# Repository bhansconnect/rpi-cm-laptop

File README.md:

<!--
SPDX-FileCopyrightText: 2021 The RPI CM Laptop Contributors

SPDX-License-Identifier: Apache-2.0
-->

# RPI CM Laptop

The goal of this project is to make a PCB that enables creation of a laptop that uses a Raspberry Pi Compute Module as the brains.
The laptop plans to use a mechanical keyboard and is meant to be a nice companion device for journaling and task management.

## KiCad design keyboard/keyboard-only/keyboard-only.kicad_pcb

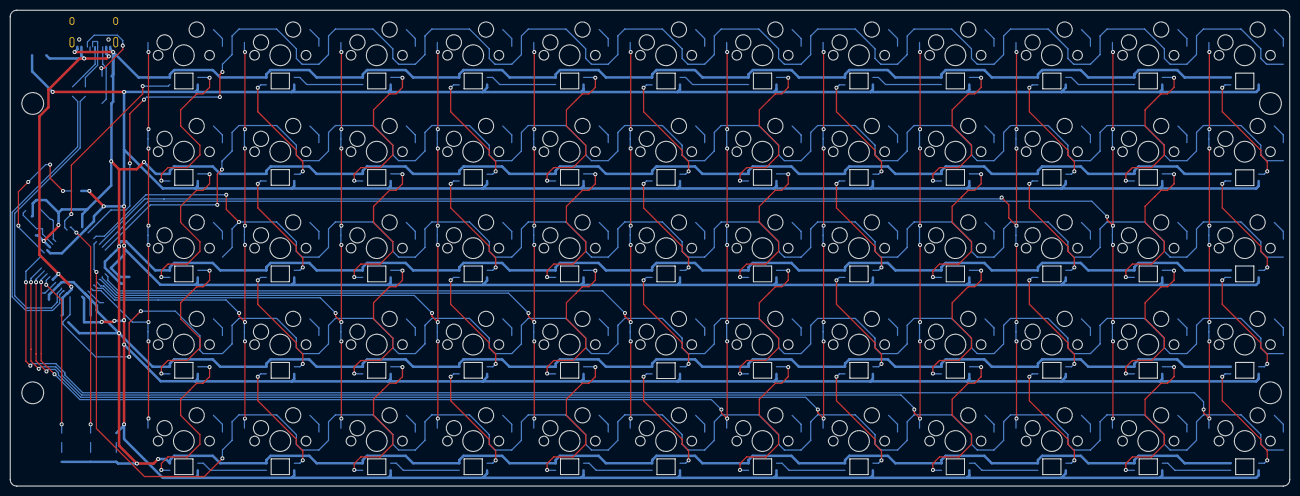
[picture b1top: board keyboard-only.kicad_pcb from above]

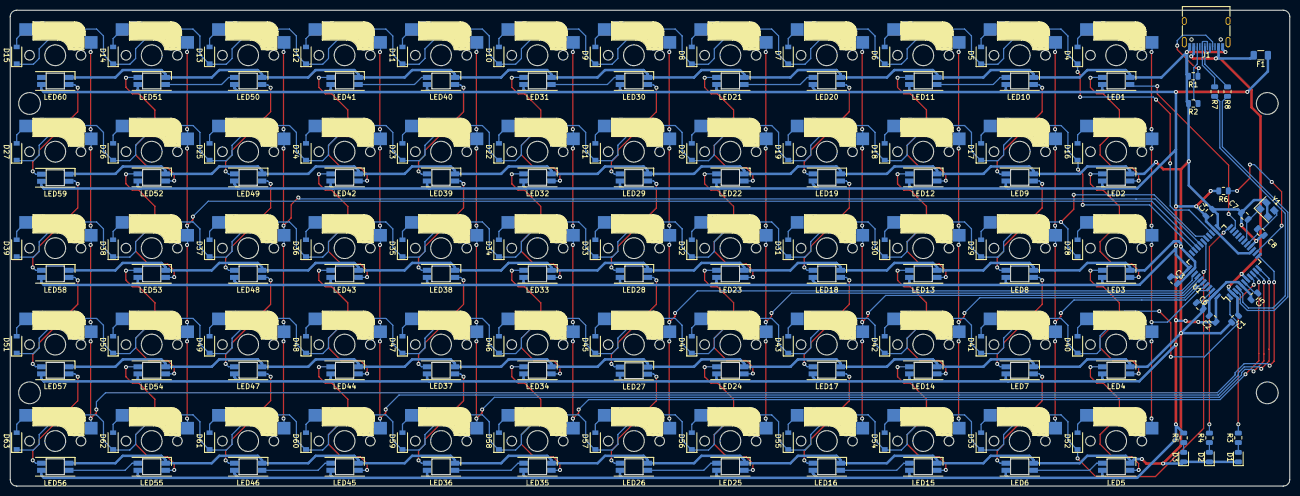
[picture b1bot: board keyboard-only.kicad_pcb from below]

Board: 2 copper layers, 252.7 x 94.0 mm, 207 parts (143 on the bottom side), 156 nets.

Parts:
C1, C3, C5: 1uF; C_0805_2012Metric
C2: 10uF; C_0805_2012Metric
C4, C6: 100nF; C_0805_2012Metric
C7, C8: 22pF; C_0805_2012Metric
D1: Yellow; LED_0805_2012Metric
D2: Green; LED_0805_2012Metric
D3: Red; LED_0805_2012Metric
D4, D5, D6, D7, D8, D9, D10, D11, D12, D13, D14, D15, D16, D17, D18, D19, D20, D21, D22, D23, D24, D25, D26, D27, D28, D29, D30, D31, D32, D33, D34, D35, D36, D37, D38, D39, D40, D41, D42, D43, D44, D45, D46, D47, D48, D49, D50, D51, D52, D53, D54, D55, D56, D57, D58, D59, D60, D61, D62, D63: D; D_SOD-123
F1: 500mA; Fuse_1206_3216Metric
J1: USB_C_Receptacle_USB2.0; USB_C_Receptacle_HRO_TYPE-C-31-M-12
LED1, LED2, LED3, LED4, LED5, LED6, LED7, LED8, LED9, LED10, LED11, LED12, LED13, LED14, LED15, LED16, LED17, LED18, LED19, LED20, LED21, LED22, LED23, LED24, LED25, LED26, LED27, LED28, LED29, LED30, LED31, LED32, LED33, LED34, LED35, LED36, LED37, LED38, LED39, LED40, LED41, LED42, LED43, LED44, LED45, LED46, LED47, LED48, LED49, LED50, LED51, LED52, LED53, LED54, LED55, LED56, LED57, LED58, LED59, LED60: YS-SK6812MINI-E
R1, R2: 5.1K; R_0805_2012Metric
R3, R4: 330; R_0805_2012Metric
R5: 1K; R_0805_2012Metric
R6: 10K; R_0805_2012Metric
R7, R8: 22; R_0805_2012Metric
Ref**: Val**; M2_HOLE_v2
Ref**#2, Ref**#3, Ref**#4: Val**; M2_HOLE_v2
SW1, SW2, SW3, SW4, SW5, SW6, SW7, SW8, SW9, SW10, SW11, SW12, SW13, SW14, SW15, SW16, SW17, SW18, SW19, SW20, SW21, SW22, SW23, SW24, SW25, SW26, SW27, SW28, SW29, SW30, SW31, SW32, SW33, SW34, SW35, SW36, SW37, SW38, SW39, SW40, SW41, SW42, SW43, SW44, SW45, SW46, SW47, SW48, SW49, SW50, SW51, SW52, SW53, SW54, SW55, SW56, SW57, SW58, SW59, SW60: SW_PUSH; CherryMX_Hotswap
U1: ATmega16U4-AU; TQFP-44_10x10mm_P0.8mm
Y1: 16MHz; Crystal_SMD_3225-4Pin_3.2x2.5mm

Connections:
COL0: SW1.1, SW13.1, SW25.1, SW37.1, SW49.1, U1.41
COL1: SW2.1, SW14.1, SW26.1, SW38.1, SW50.1, U1.40
COL2: SW3.1, SW15.1, SW27.1, SW39.1, SW51.1, U1.39
COL3: SW4.1, SW16.1, SW28.1, SW40.1, SW52.1, U1.38
COL4: SW5.1, SW17.1, SW29.1, SW41.1, SW53.1, U1.37
COL5: SW6.1, SW18.1, SW30.1, SW42.1, SW54.1, U1.36
COL6: SW7.1, SW19.1, SW31.1, SW43.1, SW55.1, U1.9
COL7: SW8.1, SW20.1, SW32.1, SW44.1, SW56.1, U1.10
COL8: SW9.1, SW21.1, SW33.1, SW45.1, SW57.1, U1.11
COL9: SW10.1, SW22.1, SW34.1, SW46.1, SW58.1, U1.29
COL10: SW11.1, SW23.1, SW35.1, SW47.1, SW59.1, U1.30
COL11: SW12.1, SW24.1, SW36.1, SW48.1, SW60.1, U1.12
D+: J1.A6, J1.B6, R7.2
D-: J1.A7, J1.B7, R8.2
GND: C1.2, C2.2, C3.2, C4.2, C5.2, C6.2, C7.2, C8.2, D1.1, D2.1, D3.1, J1.A1, J1.A12, J1.B1, J1.B12, LED1.3, LED2.3, LED3.3, LED4.3, LED5.3, LED6.3, LED7.3, LED8.3, LED9.3, LED10.3, LED11.3, LED12.3, LED13.3, LED14.3, LED15.3, LED16.3, LED17.3, LED18.3, LED19.3, LED20.3, LED21.3, LED22.3, LED23.3, LED24.3, LED25.3, LED26.3, LED27.3, LED28.3, LED29.3, LED30.3, LED31.3, LED32.3, LED33.3, LED34.3, LED35.3, LED36.3, LED37.3, LED38.3, LED39.3, LED40.3, LED41.3, LED42.3, LED43.3, LED44.3, LED45.3, LED46.3, LED47.3, LED48.3, LED49.3, LED50.3, LED51.3, LED52.3, LED53.3, LED54.3, LED55.3, LED56.3, LED57.3, LED58.3, LED59.3, LED60.3, R1.2, R2.2, U1.5, U1.15, U1.23, U1.33, U1.35, U1.43, Y1.2, Y1.4
unnamed: J1.A5, R1.1
unnamed: J1.B5, R2.1
unnamed: D3.2, R5.1
unnamed: D1.2, R3.1
unnamed: R3.2, U1.8
unnamed: D2.2, R4.1
unnamed: R4.2, U1.22
unnamed: R6.1, U1.13
unnamed: C5.1, U1.6
unnamed: C6.1, U1.42
unnamed: C7.1, U1.17, Y1.1
unnamed: C8.1, U1.16, Y1.3
unnamed: D4.2, SW1.2
unnamed: LED1.4, U1.21
unnamed: D5.2, SW2.2
unnamed: LED1.2, LED2.4
unnamed: D6.2, SW3.2
unnamed: LED2.2, LED3.4
unnamed: D7.2, SW4.2
unnamed: LED3.2, LED4.4
unnamed: D8.2, SW5.2
unnamed: LED4.2, LED5.4
unnamed: D9.2, SW6.2
unnamed: LED5.2, LED6.4
unnamed: D10.2, SW7.2
unnamed: LED6.2, LED7.4
unnamed: D11.2, SW8.2
unnamed: LED7.2, LED8.4
unnamed: D12.2, SW9.2
unnamed: LED8.2, LED9.4
unnamed: D13.2, SW10.2
unnamed: LED9.2, LED10.4
unnamed: D14.2, SW11.2
unnamed: LED10.2, LED11.4
unnamed: D15.2, SW12.2
unnamed: LED11.2, LED12.4
unnamed: D16.2, SW13.2
unnamed: LED12.2, LED13.4
unnamed: D17.2, SW14.2
unnamed: LED13.2, LED14.4
unnamed: D18.2, SW15.2
unnamed: LED14.2, LED15.4
unnamed: D19.2, SW16.2
unnamed: LED15.2, LED16.4
unnamed: D20.2, SW17.2
unnamed: LED16.2, LED17.4
unnamed: D21.2, SW18.2
unnamed: LED17.2, LED18.4
unnamed: D22.2, SW19.2
unnamed: LED18.2, LED19.4
unnamed: D23.2, SW20.2
unnamed: LED19.2, LED20.4
unnamed: D24.2, SW21.2
unnamed: LED20.2, LED21.4
unnamed: D25.2, SW22.2
unnamed: LED21.2, LED22.4
unnamed: D26.2, SW23.2
unnamed: LED22.2, LED23.4
unnamed: D27.2, SW24.2
unnamed: LED23.2, LED24.4
unnamed: D28.2, SW25.2
unnamed: LED24.2, LED25.4
unnamed: D29.2, SW26.2
unnamed: LED25.2, LED26.4
unnamed: D30.2, SW27.2
unnamed: LED26.2, LED27.4
unnamed: D31.2, SW28.2
unnamed: LED27.2, LED28.4
unnamed: D32.2, SW29.2
unnamed: LED28.2, LED29.4
unnamed: D33.2, SW30.2
unnamed: LED29.2, LED30.4
unnamed: D34.2, SW31.2
unnamed: LED30.2, LED31.4
unnamed: D35.2, SW32.2
unnamed: LED31.2, LED32.4
unnamed: D36.2, SW33.2
unnamed: LED32.2, LED33.4
unnamed: D37.2, SW34.2
unnamed: LED33.2, LED34.4
unnamed: D38.2, SW35.2
unnamed: LED34.2, LED35.4
unnamed: D39.2, SW36.2
unnamed: LED35.2, LED36.4
unnamed: D40.2, SW37.2
unnamed: LED36.2, LED37.4
unnamed: D41.2, SW38.2
unnamed: LED37.2, LED38.4
unnamed: D42.2, SW39.2
unnamed: LED38.2, LED39.4
unnamed: D43.2, SW40.2
unnamed: LED39.2, LED40.4
unnamed: D44.2, SW41.2
unnamed: LED40.2, LED41.4
unnamed: D45.2, SW42.2
unnamed: LED41.2, LED42.4
unnamed: D46.2, SW43.2
unnamed: LED42.2, LED43.4
unnamed: D47.2, SW44.2
unnamed: LED43.2, LED44.4
unnamed: D48.2, SW45.2
unnamed: LED44.2, LED45.4
unnamed: D49.2, SW46.2
unnamed: LED45.2, LED46.4
unnamed: D50.2, SW47.2
unnamed: LED46.2, LED47.4
unnamed: D51.2, SW48.2
unnamed: LED47.2, LED48.4
unnamed: D52.2, SW49.2
unnamed: LED48.2, LED49.4
unnamed: D53.2, SW50.2
unnamed: LED49.2, LED50.4
unnamed: D54.2, SW51.2
unnamed: LED50.2, LED51.4
unnamed: D55.2, SW52.2
unnamed: LED51.2, LED52.4
unnamed: D56.2, SW53.2
unnamed: LED52.2, LED53.4
unnamed: D57.2, SW54.2
unnamed: LED53.2, LED54.4
unnamed: D58.2, SW55.2
unnamed: LED54.2, LED55.4
unnamed: D59.2, SW56.2
unnamed: LED55.2, LED56.4
unnamed: D60.2, SW57.2
unnamed: LED56.2, LED57.4
unnamed: D61.2, SW58.2
unnamed: LED57.2, LED58.4
unnamed: D62.2, SW59.2
unnamed: LED58.2, LED59.4
unnamed: D63.2, SW60.2
unnamed: LED59.2, LED60.4
RD+: R7.1, U1.4
RD-: R8.1, U1.3
ROW0: D4.1, D5.1, D6.1, D7.1, D8.1, D9.1, D10.1, D11.1, D12.1, D13.1, D14.1, D15.1, U1.25
ROW1: D16.1, D17.1, D18.1, D19.1, D20.1, D21.1, D22.1, D23.1, D24.1, D25.1, D26.1, D27.1, U1.31
ROW2: D28.1, D29.1, D30.1, D31.1, D32.1, D33.1, D34.1, D35.1, D36.1, D37.1, D38.1, D39.1, U1.27
ROW3: D40.1, D41.1, D42.1, D43.1, D44.1, D45.1, D46.1, D47.1, D48.1, D49.1, D50.1, D51.1, U1.1
ROW4: D52.1, D53.1, D54.1, D55.1, D56.1, D57.1, D58.1, D59.1, D60.1, D61.1, D62.1, D63.1, U1.28
VBUS: C1.1, F1.1, J1.A4, J1.A9, J1.B4, J1.B9, U1.2, U1.7
VCC: C2.1, C3.1, C4.1, F1.2, LED1.1, LED2.1, LED3.1, LED4.1, LED5.1, LED6.1, LED7.1, LED8.1, LED9.1, LED10.1, LED11.1, LED12.1, LED13.1, LED14.1, LED15.1, LED16.1, LED17.1, LED18.1, LED19.1, LED20.1, LED21.1, LED22.1, LED23.1, LED24.1, LED25.1, LED26.1, LED27.1, LED28.1, LED29.1, LED30.1, LED31.1, LED32.1, LED33.1, LED34.1, LED35.1, LED36.1, LED37.1, LED38.1, LED39.1, LED40.1, LED41.1, LED42.1, LED43.1, LED44.1, LED45.1, LED46.1, LED47.1, LED48.1, LED49.1, LED50.1, LED51.1, LED52.1, LED53.1, LED54.1, LED55.1, LED56.1, LED57.1, LED58.1, LED59.1, LED60.1, R5.2, R6.2, U1.14, U1.24, U1.34, U1.44

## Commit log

2021-03-14 Fix minor typo
2021-03-19 Add keyboard schematic generation with scidl
2021-03-19 Label gnd as a power net to make ERC happy
2021-03-19 Add parts to pcb layout
2021-03-19 Add net name for rows and columns
2021-03-19 Flip everything to bottom of pcb
2021-03-19 Organize key matrix and diodes
2021-03-20 Setup LEDs
2021-03-20 Base ProMicro layout
2021-03-20 Reorient LEDs
2021-03-20 Layout ProMicro better
2021-03-20 Add board outline
2021-03-20 Setup USB differential pair
2021-03-20 Begin matrix wiring
2021-03-20 Add LED column wiring
2021-03-20 Complete LED data wiring
2021-03-20 Wire columns
2021-03-21 Wire all the things even if not that pretty
2021-03-21 Fix missing wires
2021-03-21 Export gerbers
2021-03-21 Update parts to match JLCPCB availability
2021-03-21 Fix reuse licensing
2021-03-21 Add BOM generation
2021-03-21 Round corners
2021-03-21 Add mounting holes
2021-03-21 Change diode to basic part
2021-03-21 Switch from xlsx to csv
2021-03-21 Flip led direction
2021-03-21 Update for JLCPCB export
